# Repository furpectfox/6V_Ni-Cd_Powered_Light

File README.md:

# 6 Ni-Cd Cells Charger

This circuit is designed to charge 5 Ni-Cd cells, in series, via a 5V USB source.

## Overview
The cells are trickle-charged at a constant current of 60mA (0.1C). The current is generated by a simple transistor constant current circuit. Care must be taken so that the voltage across the transistor is minimal so that power consumption is low and the transistor won't heat up too much. Charging will typically be completed after around 16 hours. However, because the charging current is low, it prevents the gas-venting effect in Ni-Cd batteries, allowing the cells to be left on the charger indefinitely.

Challenge: Since each cell has a nominal voltage of 1.2V, the total voltage of 5 cells in series is 6V, which is higher than the 5V USB source. As the cells are charged up, the voltage of each cell rises closer to 1.4V, thus increasing the total voltage further. In addition, other components of the charging circuit increases the total voltage by around 2V (voltage across current-set resistor, voltage across transistor, voltage across protection diode).

Solution: Boost the 5V USB to at 9V or more with a simple boost converter circuit. 'Simple' because this circuit does not have any feedback (at all!) to ensure the voltage stays constant if the load changes. I figured this would be fine because the current consumed by the load (the charging circuit) would be relatively constant. After some testing, I found this to be the case.

## Features
- There is a 1ohm resistor in series with the Ni-Cd battery pack, which allows the user to 'measure' the charging current by measuring the voltage across the resistor, where I(charging) = V(R-1ohm) / 1ohm

## Note
- The provided schematic includes the boost converter and constant-current charging circuit for the cells. It also provides screw-terminal connections for a XL4001E1 constant-currrent LED driver module. 

## Future Improvements
- Even though the circuit works fine at the moment, some type of feedback control should be added to the boost converter to make sure that the output voltage stays constant, for safety and efficiency concerns.

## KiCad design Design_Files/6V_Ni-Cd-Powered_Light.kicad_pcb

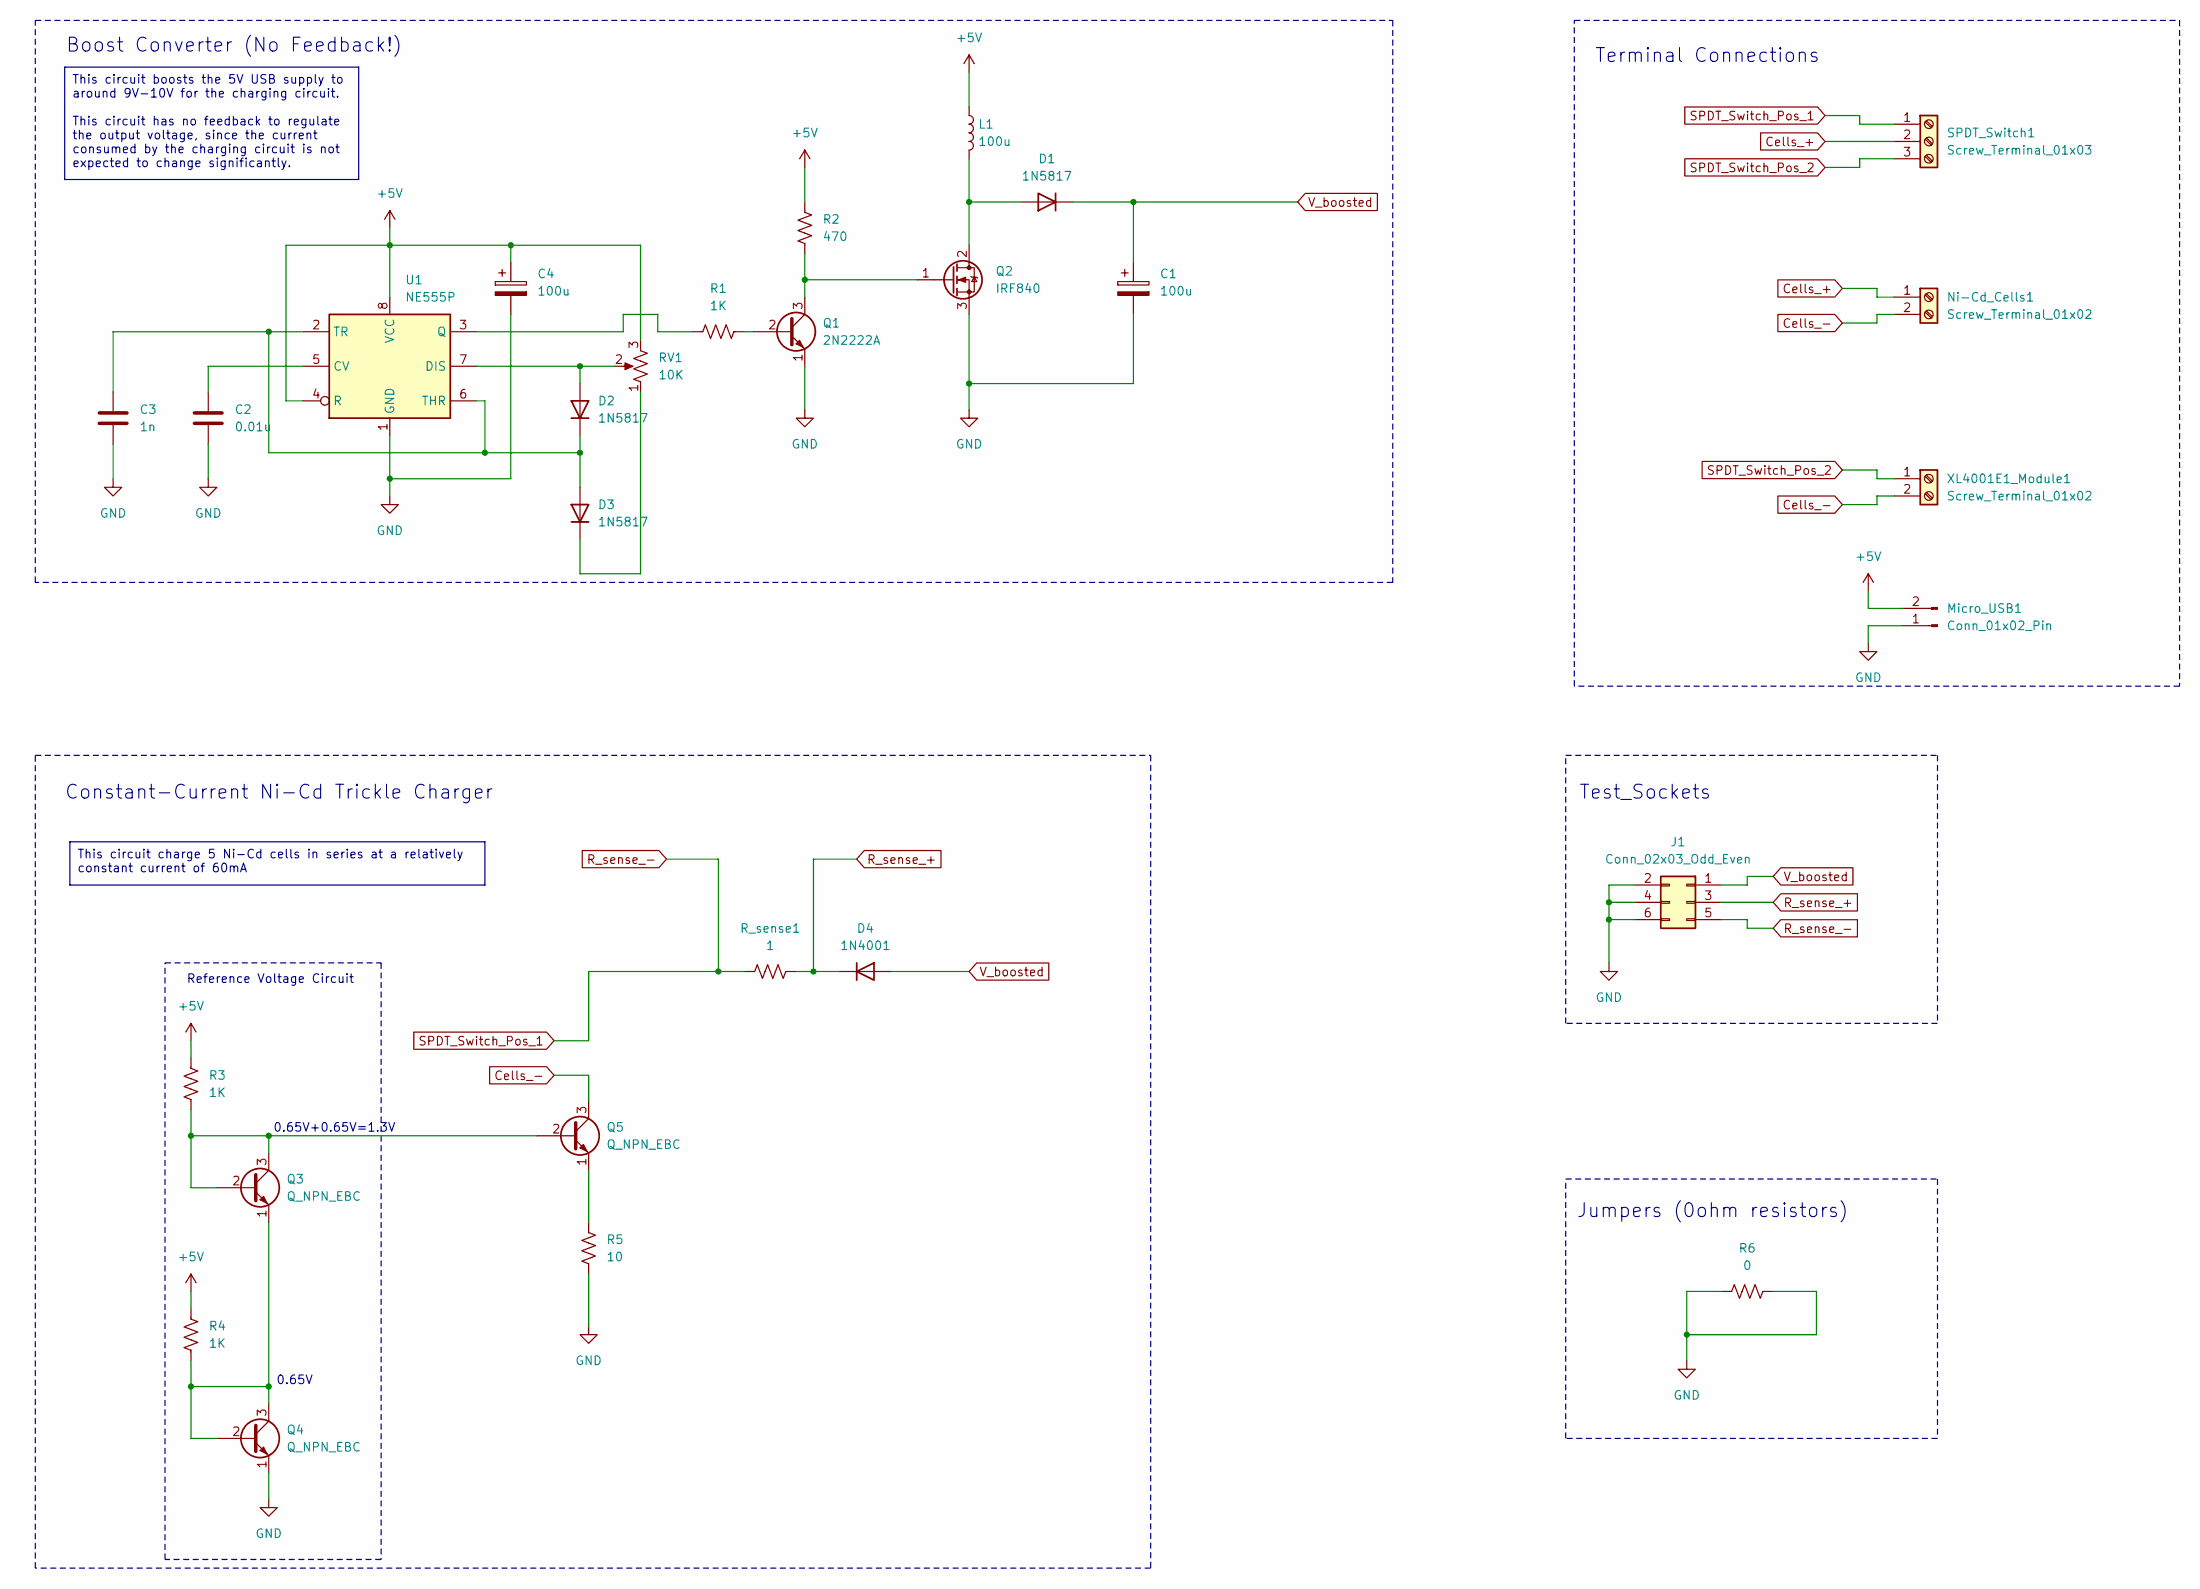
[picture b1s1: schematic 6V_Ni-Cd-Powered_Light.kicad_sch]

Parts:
C1, C4: 100u; CP_Radial_D5.0mm_P2.50mm
C2: 0.01u; C_Disc_D3.8mm_W2.6mm_P2.50mm
C3: 1n; C_Disc_D3.8mm_W2.6mm_P2.50mm
D1, D2, D3: 1N5817; D_A-405_P7.62mm_Horizontal
D4: 1N4001; D_A-405_P7.62mm_Horizontal
J1: Conn_02x03_Odd_Even; PinSocket_2x03_P2.54mm_Vertical
L1: 100u; L_Axial_L5.0mm_D3.6mm_P10.00mm_Horizontal_Murata_BL01RN1A2A2
Micro_USB1: Conn_01x02_Pin; PinHeader_1x02_P2.54mm_Vertical
Ni-Cd_Cells1: Screw_Terminal_01x02; TerminalBlock_Altech_AK300-2_P5.00mm
Q1: 2N2222A; TO-92L_Inline_Wide
Q2: IRF840; TO-126-3_Vertical
Q3, Q4, Q5: Q_NPN_EBC; TO-92L_Inline_Wide
R1, R3, R4: 1K; R_Axial_DIN0207_L6.3mm_D2.5mm_P7.62mm_Horizontal
R2: 470; R_Axial_DIN0207_L6.3mm_D2.5mm_P7.62mm_Horizontal
R5: 10; R_Axial_DIN0207_L6.3mm_D2.5mm_P7.62mm_Horizontal
R6: 0; R_Axial_DIN0207_L6.3mm_D2.5mm_P7.62mm_Horizontal
RV1: 10K; Potentiometer_Piher_PT-10-V05_Vertical
R_sense1: 1; R_Axial_DIN0207_L6.3mm_D2.5mm_P7.62mm_Horizontal
SPDT_Switch1: Screw_Terminal_01x03; TerminalBlock_Altech_AK300-3_P5.00mm
U1: NE555P; DIP-8_W7.62mm
XL4001E1_Module1: Screw_Terminal_01x02; TerminalBlock_Altech_AK300-2_P5.00mm

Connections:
+5V: C4.1, L1.1, Micro_USB1.2, R2.2, R3.2, R4.2, RV1.3, U1.4 (R), U1.8 (VCC)
Cells_+: Ni-Cd_Cells1.1, SPDT_Switch1.2
Cells_-: Ni-Cd_Cells1.2, Q5.3 (C), XL4001E1_Module1.2
GND: C1.2, C2.2, C3.2, C4.2, J1.2, J1.4, J1.6, Micro_USB1.1, Q1.1 (E), Q2.3 (S), Q4.1 (E), R5.1, R6.1, R6.2, U1.1 (GND)
unnamed: D1.2 (A), L1.2, Q2.2 (D)
unnamed: D2.2 (A), RV1.2, U1.7 (DIS)
unnamed: C3.1, D2.1 (K), D3.2 (A), U1.2 (TR), U1.6 (THR)
unnamed: D3.1 (K), RV1.1
unnamed: Q1.2 (B), R1.2
unnamed: Q1.3 (C), Q2.1 (G), R2.1
unnamed: Q3.2 (B), Q3.3 (C), Q5.2 (B), R3.1
unnamed: Q3.1 (E), Q4.2 (B), Q4.3 (C), R4.1
unnamed: Q5.1 (E), R5.2
unnamed: C2.1, U1.5 (CV)
unnamed: R1.1, U1.3 (Q)
R_sense_+: D4.1 (K), J1.3, R_sense1.1
R_sense_-: J1.5, R_sense1.2, SPDT_Switch1.1
SPDT_Switch_Pos_2: SPDT_Switch1.3, XL4001E1_Module1.1
V_boosted: C1.1, D1.1 (K), D4.2 (A), J1.1

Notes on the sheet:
This circuit boosts the 5V USB supply to around 9V-10V for the charging circuit. This circuit has no feedback to regulate the output voltage, since the current consumed by the charging circuit is not expected to change significantly.
This circuit charge 5 Ni-Cd cells in series at a relatively constant current of 60mA
Boost Converter (No Feedback!)
0.65V
Terminal Connections
Test_Sockets
0.65V+0.65V=1.3V
Reference Voltage Circuit
Constant-Current Ni-Cd Trickle Charger
Jumpers (0ohm resistors)

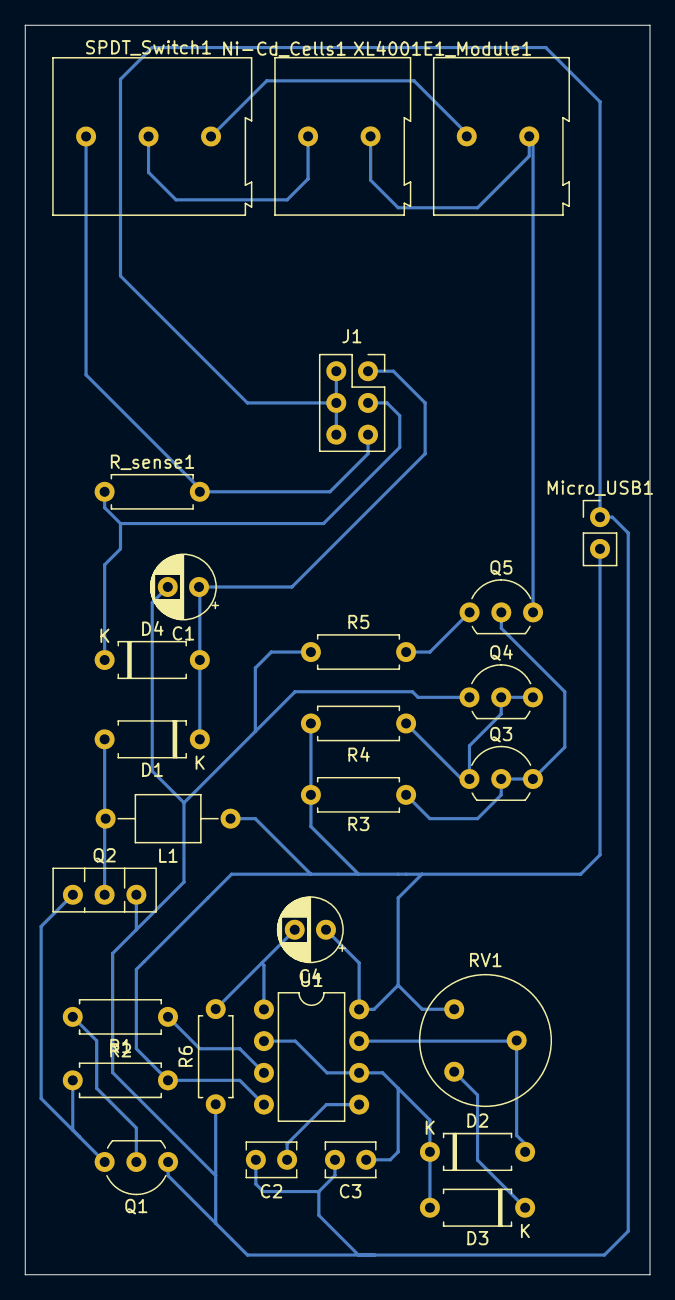
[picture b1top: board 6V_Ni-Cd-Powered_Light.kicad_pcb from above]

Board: 2 copper layers, 50.0 x 100.0 mm, 28 parts (0 on the bottom side), 19 nets.

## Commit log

2024-08-08 Initial commit: Upload project files for Ni-Cd battery powered light
2024-08-08 Add images. Edit README.md
